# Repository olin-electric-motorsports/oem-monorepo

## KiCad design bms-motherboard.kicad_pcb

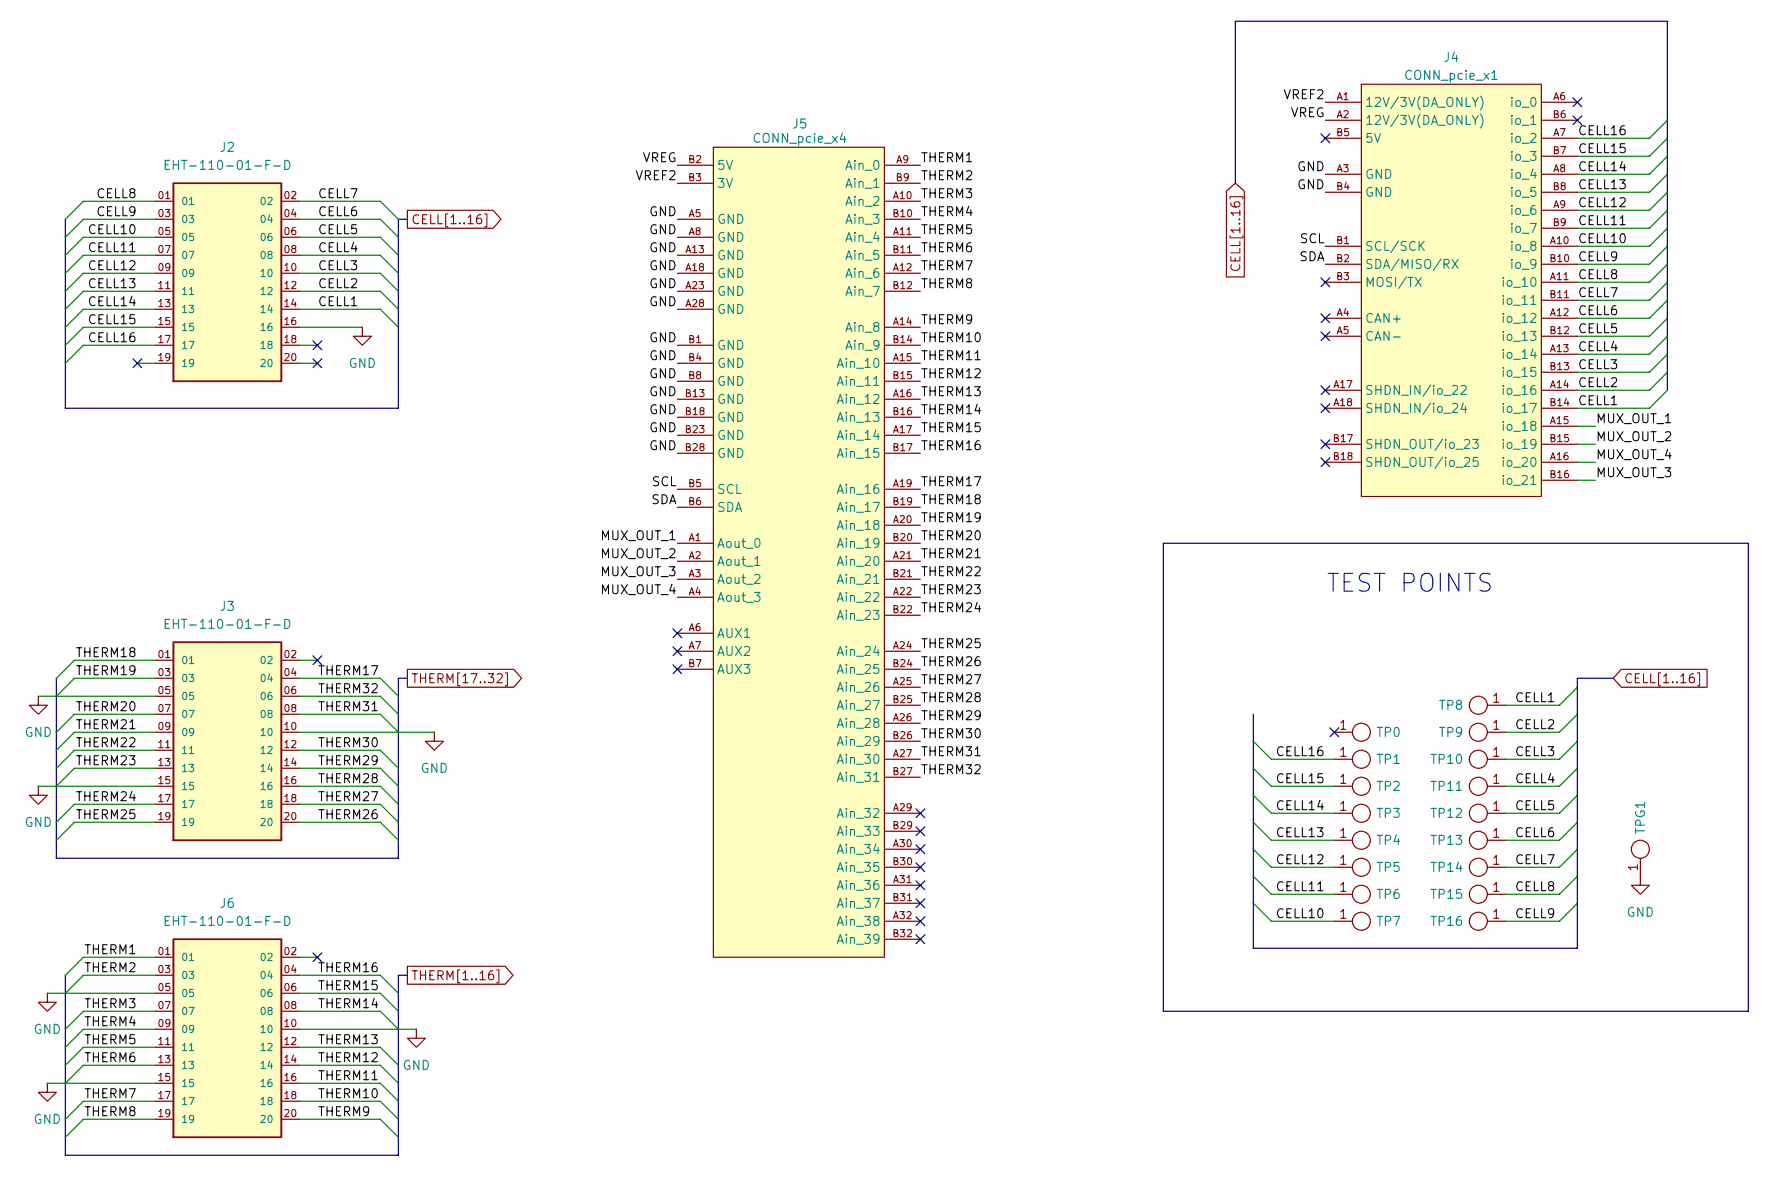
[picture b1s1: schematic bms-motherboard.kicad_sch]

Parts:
J2, J3, J6: EHT-110-01-F-D; SAMTEC_EHT-110-01-X-D (J_EHT-110-01-F-D); MPN EHT-110-01-F-D
J4: CONN_pcie_x1; te_pcie_x1_connector
J5: CONN_pcie_x4; te_pcie_x4_connector
TP0, TP1, TP2, TP3, TP4, TP5, TP6, TP7, TP8, TP9, TP10, TP11, TP12, TP13, TP14, TP15, TP16: TP_SMD; Test_Point_SMD; MPN 5019
TPG1: TP_SMD; Test_Point_SMD; MPN 5019

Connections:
/MUX_OUT_1: J4.A15 (io_18), J5.A1 (Aout_0)
/MUX_OUT_2: J4.B15 (io_19), J5.A2 (Aout_1)
/MUX_OUT_3: J4.B16 (io_21), J5.A3 (Aout_2)
/MUX_OUT_4: J4.A16 (io_20), J5.A4 (Aout_3)
/SCL: J4.B1 (SCL/SCK), J5.B5 (SCL)
/SDA: J4.B2 (SDA/MISO/RX), J5.B6 (SDA)
/VREF2: J4.A1 (12V/3V(DA_ONLY)), J5.B3 (3V)
/VREG: J4.A2 (12V/3V(DA_ONLY)), J5.B2 (5V)
CELL1: J2.14, J4.B14 (io_17), TP8.1
CELL2: J2.12, J4.A14 (io_16), TP9.1
CELL3: J2.10, J4.B13 (io_15), TP10.1
CELL4: J2.08, J4.A13 (io_14), TP11.1
CELL5: J2.06, J4.B12 (io_13), TP12.1
CELL6: J2.04, J4.A12 (io_12), TP13.1
CELL7: J2.02, J4.B11 (io_11), TP14.1
CELL8: J2.01, J4.A11 (io_10), TP15.1
CELL9: J2.03, J4.B10 (io_9), TP16.1
CELL10: J2.05, J4.A10 (io_8), TP7.1
CELL11: J2.07, J4.B9 (io_7), TP6.1
CELL12: J2.09, J4.A9 (io_6), TP5.1
CELL13: J2.11, J4.B8 (io_5), TP4.1
CELL14: J2.13, J4.A8 (io_4), TP3.1
CELL15: J2.15, J4.B7 (io_3), TP2.1
CELL16: J2.17, J4.A7 (io_2), TP1.1
GND: J2.16, J3.05, J3.10, J3.15, J4.A3 (GND), J4.B4 (GND), J5.A5 (GND), J5.A8 (GND), J5.A13 (GND), J5.A18 (GND), J5.A23 (GND), J5.A28 (GND), J5.B1 (GND), J5.B4 (GND), J5.B8 (GND), J5.B13 (GND), J5.B18 (GND), J5.B23 (GND), J5.B28 (GND), J6.05, J6.10, J6.15, TPG1.1; also elsewhere on the board
THERM1: J5.A9 (Ain_0), J6.01
THERM2: J5.B9 (Ain_1), J6.03
THERM3: J5.A10 (Ain_2), J6.07
THERM4: J5.B10 (Ain_3), J6.09
THERM5: J5.A11 (Ain_4), J6.11
THERM6: J5.B11 (Ain_5), J6.13
THERM7: J5.A12 (Ain_6), J6.17
THERM8: J5.B12 (Ain_7), J6.19
THERM9: J5.A14 (Ain_8), J6.20
THERM10: J5.B14 (Ain_9), J6.18
THERM11: J5.A15 (Ain_10), J6.16
THERM12: J5.B15 (Ain_11), J6.14
THERM13: J5.A16 (Ain_12), J6.12
THERM14: J5.B16 (Ain_13), J6.08
THERM15: J5.A17 (Ain_14), J6.06
THERM16: J5.B17 (Ain_15), J6.04
THERM17: J3.04, J5.A19 (Ain_16)
THERM18: J3.01, J5.B19 (Ain_17)
THERM19: J3.03, J5.A20 (Ain_18)
THERM20: J3.07, J5.B20 (Ain_19)
THERM21: J3.09, J5.A21 (Ain_20)
THERM22: J3.11, J5.B21 (Ain_21)
THERM23: J3.13, J5.A22 (Ain_22)
THERM24: J3.17, J5.B22 (Ain_23)
THERM25: J3.19, J5.A24 (Ain_24)
THERM26: J3.20, J5.B24 (Ain_25)
THERM27: J3.18, J5.A25 (Ain_26)
THERM28: J3.16, J5.B25 (Ain_27)
THERM29: J3.14, J5.A26 (Ain_28)
THERM30: J3.12, J5.B26 (Ain_29)
THERM31: J3.08, J5.A27 (Ain_30)
THERM32: J3.06, J5.B27 (Ain_31)

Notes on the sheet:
TEST POINTS

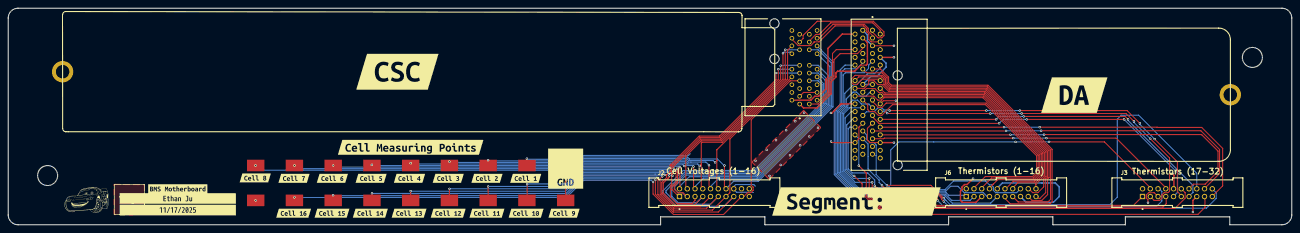
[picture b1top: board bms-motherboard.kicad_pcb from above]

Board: 2 copper layers, 331.3 x 55.9 mm, 49 parts (0 on the bottom side), 57 nets.

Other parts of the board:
H1, H2: CONN_MountingHole; PCIe_Mount
kibuzzard-691BC27F: G***; kibuzzard-691BC27F
kibuzzard-691BC245: G***; kibuzzard-691BC245
kibuzzard-691BC298: G***; kibuzzard-691BC298
kibuzzard-6747A1EF: G***; kibuzzard-6747A1EF
kibuzzard-6747A1F5: G***; kibuzzard-6747A1F5
kibuzzard-6747A1FA: G***; kibuzzard-6747A1FA
kibuzzard-6747A20D: G***; kibuzzard-6747A20D
kibuzzard-6747A21A: G***; kibuzzard-6747A21A
kibuzzard-6747A21D: G***; kibuzzard-6747A21D
kibuzzard-6747A22C: G***; kibuzzard-6747A22C
kibuzzard-6747A22F: G***; kibuzzard-6747A22F
kibuzzard-6747A069: G***; kibuzzard-6747A069
kibuzzard-6747A200: G***; kibuzzard-6747A200
kibuzzard-6747A204: G***; kibuzzard-6747A204
kibuzzard-6747A209: G***; kibuzzard-6747A209
kibuzzard-6747A211: G***; kibuzzard-6747A211
kibuzzard-6747A215: G***; kibuzzard-6747A215
kibuzzard-6747A222: G***; kibuzzard-6747A222
kibuzzard-6747A229: G***; kibuzzard-6747A229
kibuzzard-6747A319: G***; kibuzzard-6747A319
kibuzzard-6747A384: G***; kibuzzard-6747A384
kibuzzard-6747F2A5: G***; kibuzzard-6747F2A5
kibuzzard-67479E66: G***; kibuzzard-67479E66
kibuzzard-67479E86: G***; kibuzzard-67479E86

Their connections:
GND: H2.1; also elsewhere on the board

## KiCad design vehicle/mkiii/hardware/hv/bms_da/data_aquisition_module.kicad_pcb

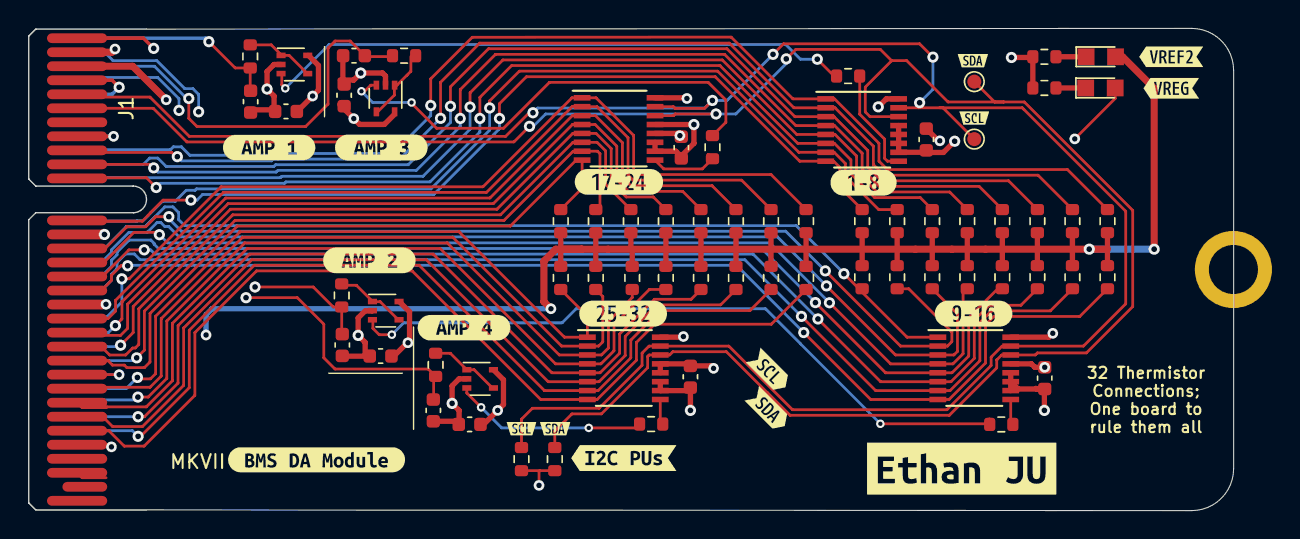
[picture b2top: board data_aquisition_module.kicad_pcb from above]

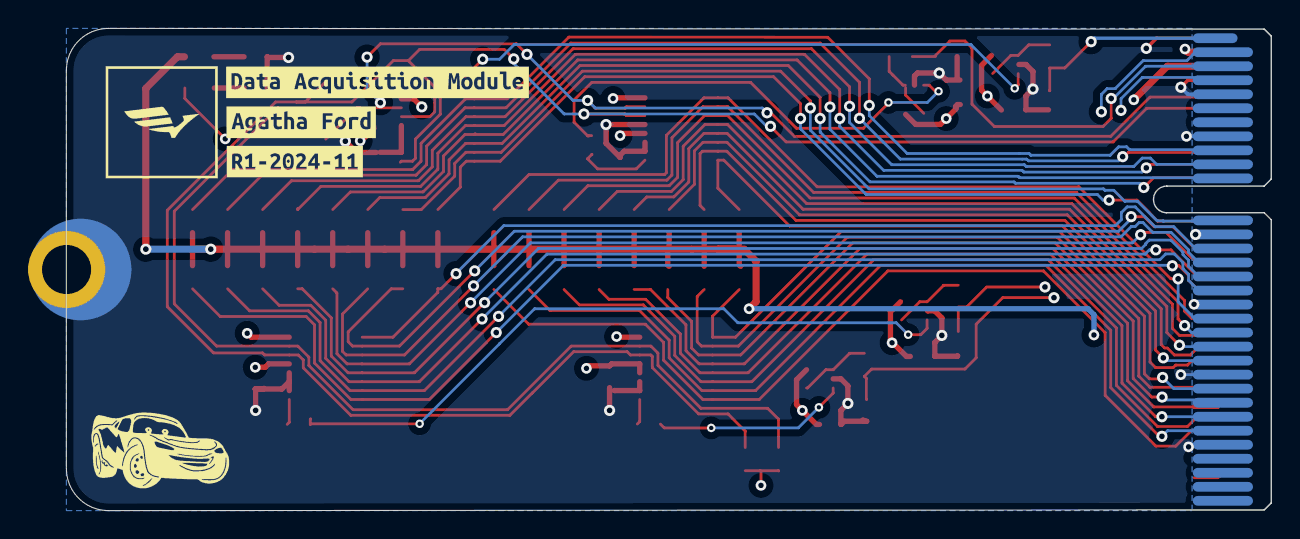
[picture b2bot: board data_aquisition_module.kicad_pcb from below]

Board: 4 copper layers, 86.0 x 34.4 mm, 92 parts (3 on the bottom side), 55 nets.

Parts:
C1, C2, C3, C4: C_1uF; C_0603
C5, C6, C7, C8, C9, C10, C11, C12: 1uF; C_0603
H2: CONN_MountingHole; PCIe_Mount
J1: CONN_pcie_x4; pcie_x4
PD1, PD2: WHITE; CHIPLED_0805
R1, R2, R3, R4, R5, R6, R7, R8, R9, R10, R11, R12, R13, R14, R15, R16, R17, R18, R19, R20, R21, R22, R23, R24, R25, R26, R27, R28, R29, R30, R31, R32: R_100K; R_0603
R33, R35, R37, R39: 1M; R_0603
R34, R36, R38, R40: 3.3K; R_0603
R41, R42: 1KR; R_0603
R43, R44: 4.7K; R_0603
TP1, TP2: TP_1mm; TestPoint_Pad_D1.0mm
U1, U2, U3, U4: LTC1380IGN; SSOP-16_3.9x4.9mm_P0.635mm
U5, U6, U7, U8: MCP6001T-I-LT; SOT-353_SC-70-5
kibuzzard-63A54BB0: G***; kibuzzard-63A54BB0
kibuzzard-63A54BCB: G***; kibuzzard-63A54BCB
kibuzzard-63A54BE3: G***; kibuzzard-63A54BE3
kibuzzard-63BF51CA: G***; kibuzzard-63BF51CA
kibuzzard-63BF55B8: G***; kibuzzard-63BF55B8
kibuzzard-63BF55D1: G***; kibuzzard-63BF55D1
kibuzzard-672C3C6B, kibuzzard-672C3C6B#2: G***; kibuzzard-672C3C6B
kibuzzard-672C3C52, kibuzzard-672C3C52#2: G***; kibuzzard-672C3C52
kibuzzard-672C38BF: G***; kibuzzard-672C38BF
kibuzzard-672D5DF4: G***; kibuzzard-672D5DF4
kibuzzard-673B8AB7: G***; kibuzzard-673B8AB7
kibuzzard-673B8ABD: G***; kibuzzard-673B8ABD
kibuzzard-673B8BCC: G***; kibuzzard-673B8BCC
kibuzzard-673B8DE4: G***; kibuzzard-673B8DE4
kibuzzard-673B8DEE: G***; kibuzzard-673B8DEE
kibuzzard-691BC3E8: G***; kibuzzard-691BC3E8
kibuzzard-66171EA1: G***; kibuzzard-66171EA1
kibuzzard-66171EC5: G***; kibuzzard-66171EC5
kibuzzard-661723CB: G***; kibuzzard-661723CB
kibuzzard-661723F5: G***; kibuzzard-661723F5

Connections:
/MUX_1_OUT: C12.1, J1.A1 (Aout_0), R34.1
/MUX_2_OUT: C10.1, J1.A2 (Aout_1), R36.1
/MUX_3_OUT: C8.1, J1.A3 (Aout_2), R38.1
/MUX_4_OUT: C6.1, J1.A4 (Aout_3), R40.1
/SCL: J1.B5 (SCL), R43.1, TP1.1, U1.15 (SCL), U2.15 (SCL), U3.15 (SCL), U4.15 (SCL)
/SDA: J1.B6 (SDA), R44.1, TP2.1, U1.14 (SDA), U2.14 (SDA), U3.14 (SDA), U4.14 (SDA)
/THERM_1: J1.A9 (Ain_0), R1.2, U1.1 (S0)
/THERM_2: J1.B9 (Ain_1), R2.2, U1.2 (S1)
/THERM_3: J1.A10 (Ain_2), R3.2, U1.3 (S2)
/THERM_4: J1.B10 (Ain_3), R4.2, U1.4 (S3)
/THERM_5: J1.A11 (Ain_4), R5.2, U1.5 (S4)
/THERM_6: J1.B11 (Ain_5), R6.2, U1.6 (S5)
/THERM_7: J1.A12 (Ain_6), R7.2, U1.7 (S6)
/THERM_8: J1.B12 (Ain_7), R8.2, U1.8 (S7)
/THERM_9: J1.A14 (Ain_8), R9.2, U2.1 (S0)
/THERM_10: J1.B14 (Ain_9), R10.2, U2.2 (S1)
/THERM_11: J1.A15 (Ain_10), R11.2, U2.3 (S2)
/THERM_12: J1.B15 (Ain_11), R12.2, U2.4 (S3)
/THERM_13: J1.A16 (Ain_12), R13.2, U2.5 (S4)
/THERM_14: J1.B16 (Ain_13), R14.2, U2.6 (S5)
/THERM_15: J1.A17 (Ain_14), R15.2, U2.7 (S6)
/THERM_16: J1.B17 (Ain_15), R16.2, U2.8 (S7)
/THERM_17: J1.A19 (Ain_16), R17.2, U3.1 (S0)
/THERM_18: J1.B19 (Ain_17), R18.2, U3.2 (S1)
/THERM_19: J1.A20 (Ain_18), R19.2, U3.3 (S2)
/THERM_20: J1.B20 (Ain_19), R20.2, U3.4 (S3)
/THERM_21: J1.A21 (Ain_20), R21.2, U3.5 (S4)
/THERM_22: J1.B21 (Ain_21), R22.2, U3.6 (S5)
/THERM_23: J1.A22 (Ain_22), R23.2, U3.7 (S6)
/THERM_24: J1.B22 (Ain_23), R24.2, U3.8 (S7)
/THERM_25: J1.A24 (Ain_24), R25.2, U4.1 (S0)
/THERM_26: J1.B24 (Ain_25), R26.2, U4.2 (S1)
/THERM_27: J1.A25 (Ain_26), R27.2, U4.3 (S2)
/THERM_28: J1.B25 (Ain_27), R28.2, U4.4 (S3)
/THERM_29: J1.A26 (Ain_28), R29.2, U4.5 (S4)
/THERM_30: J1.B26 (Ain_29), R30.2, U4.6 (S5)
/THERM_31: J1.A27 (Ain_30), R31.2, U4.7 (S6)
/THERM_32: J1.B27 (Ain_31), R32.2, U4.8 (S7)
/VREF2: J1.B3 (3V), PD2.2 (A), R1.1, R2.1, R3.1, R4.1, R5.1, R6.1, R7.1, R8.1, R9.1, R10.1, R11.1, R12.1, R13.1, R14.1, R15.1, R16.1, R17.1, R18.1, R19.1, R20.1, R21.1, R22.1, R23.1, R24.1, R25.1, R26.1, R27.1, R28.1, R29.1, R30.1, R31.1, R32.1
/VREG: C1.1, C2.1, C3.1, C4.1, C5.1, C7.1, C9.1, C11.1, J1.B2 (5V), PD1.2 (A), R43.2, R44.2, U1.16 (VCC), U2.13 (A0), U2.16 (VCC), U3.12 (A1), U3.16 (VCC), U4.12 (A1), U4.13 (A0), U4.16 (VCC), U5.5 (V+), U6.5 (V+), U7.5 (V+), U8.5 (V+)
GND: C1.2, C2.2, C3.2, C4.2, C5.2, C6.2, C7.2, C8.2, C9.2, C10.2, C11.2, C12.2, H2.1, J1.A5 (GND), J1.A8 (GND), J1.A13 (GND), J1.A18 (GND), J1.A23 (GND), J1.A28 (GND), J1.B1 (GND), J1.B4 (GND), J1.B8 (GND), J1.B13 (GND), J1.B18 (GND), J1.B23 (GND), J1.B28 (GND), R41.2, R42.2, U1.10 (VEE), U1.11 (GND), U1.12 (A1), U1.13 (A0), U2.10 (VEE), U2.11 (GND), U2.12 (A1), U3.10 (VEE), U3.11 (GND), U3.13 (A0), U4.10 (VEE), U4.11 (GND), U5.2 (V-), U6.2 (V-), U7.2 (V-), U8.2 (V-)
unnamed: PD1.1 (K), R41.1
unnamed: PD2.1 (K), R42.1
unnamed: R33.1, U1.9 (D0)
unnamed: R35.1, U2.9 (D0)
unnamed: R37.1, U3.9 (D0)
unnamed: R39.1, U4.9 (D0)
unnamed: R39.2, U5.3 (+)
unnamed: R40.2, U5.1, U5.4 (-)
unnamed: R37.2, U6.3 (+)
unnamed: R38.2, U6.1, U6.4 (-)
unnamed: R35.2, U7.3 (+)
unnamed: R36.2, U7.1, U7.4 (-)
unnamed: R33.2, U8.3 (+)
unnamed: R34.2, U8.1, U8.4 (-)

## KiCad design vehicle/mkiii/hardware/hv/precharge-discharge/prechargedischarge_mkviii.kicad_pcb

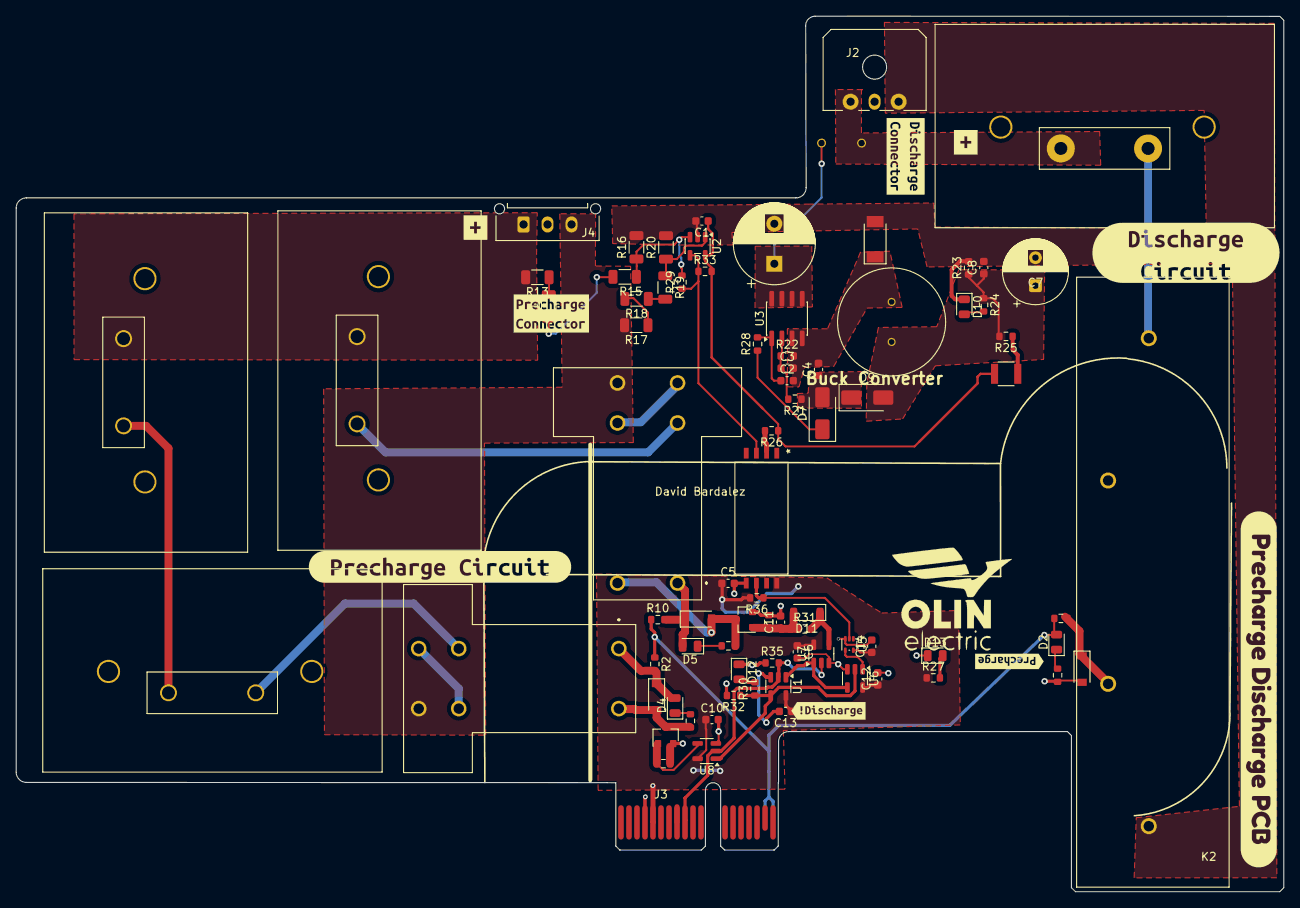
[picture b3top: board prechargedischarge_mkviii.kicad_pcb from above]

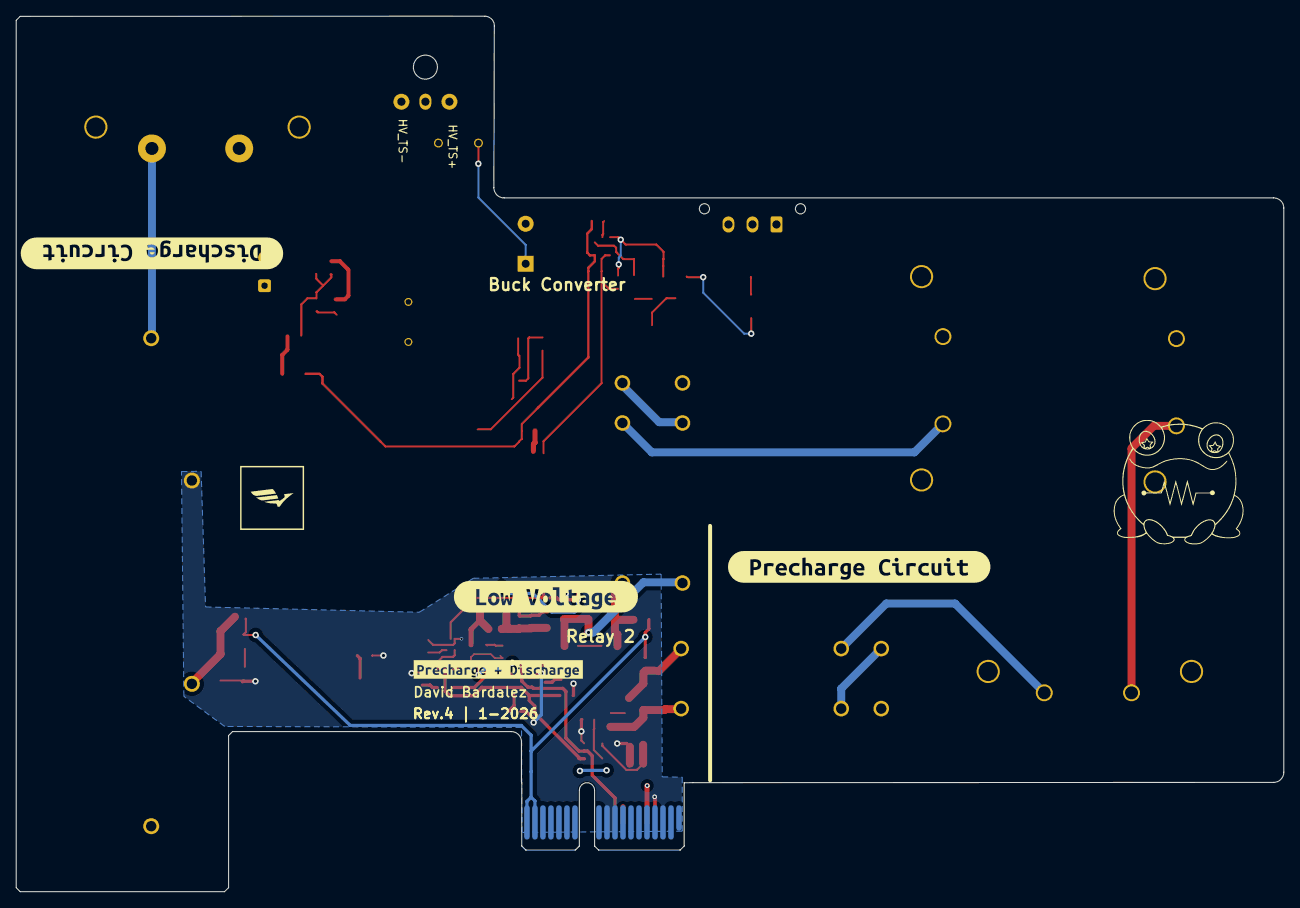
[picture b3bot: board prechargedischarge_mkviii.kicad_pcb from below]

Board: 2 copper layers, 158.4 x 109.4 mm, 94 parts (4 on the bottom side), 49 nets.

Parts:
C1, C5, C6, C10, C14: 0.1 µF; C_0603_1608Metric
C2: C_2.2uF; C_0603_1608Metric
C3: C_470pF; C_0603_1608Metric
C4: C_.22uF; C_0603_1608Metric
C7: 100uF+; CP_Radial_D8.0mm_P3.50mm
C8: C_1uF; C_0603_1608Metric
C9: 10uF+; CP_Radial_D10.0mm_P5.00mm
C11: C_2.2uF_25V; C_0603_1608Metric
C12, C13: C_0.1uF; C_0603_1608Metric
D1, D3, D6: SS110LW; D_SOD-123
D2, D4, D5: LED_WHITE; D_0805_2012Metric
D7, D9: STTH1R06AF; D_SMA
D8: STTH1R06AF; D_SOD-128
D10, D13: LED_WHITE; LED_0805_2012Metric
D11: 1N4148W; D_SOD-123
D12: BSPD_TRIP_LED; D_0805_2012Metric
F1: F_21mA_420V
F2: F_500mA_16V; Fuse_1210
J2: Conn_01x03_Pin; Molex_Micro-Fit_3.0_43650-0300_1x03_P3.00mm_Horizontal
J3: CONN_pcie_x1; pcie_x1
J4: Conn_01x03_Pin; Molex_Micro-Fit_3.0_43650-0315_1x03_P3.00mm_Vertical
K1, K3: G2RG-2A-X_DC12; K_Relay_DPST_NO_10A_12V_TH
K2: 3350-4275-126; Relay_Comus_3350
L1: L_1.2mH
Q1, Q2: SSM3K333R; SOT-23F
R1: 10KR; R_0603
R2, R10: 12R; R_0603_1608Metric
R3, R4: 560R-100W; R_TO247-Heatsink
R5: 12R; R_0603
R6: 3KR-100W; R_TO247-Heatsink
R7, R8, R11: 1KR; R_0603
R9: 120R-100W; R_TO247-Heatsink
R12: 270kR; R_0603
R13, R14, R17, R18: 2.2 MΩ; R_1206_3216Metric
R15, R19: 330 kΩ; R_1206_3216Metric
R16: 36 kΩ; R_1206_3216Metric
R20: 25 kΩ; R_1206_3216Metric
R21: R_71.5K; R_0603_1608Metric
R22: R_6.04K; R_0603_1608Metric
R23: R_3K; R_0603_1608Metric
R24, R27, R30: R_1K; R_0603_1608Metric
R25: R_0_2512; R_0603_1608Metric
R26: 330Ω; R_0603_1608Metric
R28, R32: R_10K; R_0603_1608Metric
R29: R_4.7M; R_0603_1608Metric
R31: R_71.5k; R_0603_1608Metric
R33, R36: R_10k; R_0603_1608Metric
R35: 100 kΩ; R_0603_1608Metric
U1, U6: U_GATE_SN74LVC1G02DBVR; SOT-23-5
U2: LM397; SOT-23-5
U3: MP9488; SOIC-8_3.9x4.9mm_P1.27mm
U4: ACNT-H50L-500E
U5: 74LVC1GU04DRL; SOT-553
U7, U8: SN74LVC1G08DBVR; SOT-23-5
kibuzzard-679E7E49, kibuzzard-679E7E49#2: G***; kibuzzard-679E7E49
kibuzzard-679E7E71: G***; kibuzzard-679E7E71
kibuzzard-679E7EA1: G***; kibuzzard-679E7EA1
kibuzzard-679E816B: G***; kibuzzard-679E816B
kibuzzard-679E8163: G***; kibuzzard-679E8163
kibuzzard-679E8270: G***; kibuzzard-679E8270
kibuzzard-679EBF0B, kibuzzard-679EBF0B#2: G***; kibuzzard-679EBF0B
kibuzzard-6784D6A3: G***; kibuzzard-6784D6A3
kibuzzard-6784D6E2: G***; kibuzzard-6784D6E2
kibuzzard-6784D698: G***; kibuzzard-6784D698
kibuzzard-639639B8: G***; kibuzzard-639639B8

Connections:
+5V: C5.1, C6.1, C10.1, C12.1, C13.1, C14.1, J3.B5 (5V), R27.1, R36.2, U1.5 (VCC), U4.8, U5.5 (VCC), U6.5 (VCC), U7.5 (VCC), U8.5 (VCC)
/+5V_TS_FUSED: C1.1, F2.1, R26.1, R33.2, U2.5 (V+)
/DONE_ISO: R36.1, U4.6, U5.2
/DONE_ISO_N: U5.4, U6.1 (in)
/DONE_LATCHED: U1.1 (in), U6.4 (out), U7.1
/DONE_LATCHED_N: R30.1, R32.1, U1.4 (out), U6.2 (in), U8.1
/FB: C3.1, R21.2, R22.1, U3.2 (FB)
/FINAL_SHUTDOWN: D2.2 (A), J3.A17 (SHDN_IN/io_22), J3.A18 (SHDN_IN/io_24), R2.1, R5.1, R10.1
/HV_BAT+: J4.1, R4.1, R9.1, R13.2
/HV_TS+: F1.2, J2.1, R6.1
/HV_TS+_Fuse: J4.3, K1.5 (NO_(-)), K3.5 (NO_(-)), R17.2
/HV_TS-: C1.2, C7.2, C8.2, C9.2, D8.2 (A), D10.1 (K), J2.3, K2.1, R16.2, R20.2, R23.2, U2.2 (V-)
/PRECHARGE_DONE_N: R29.1, R33.1, U2.4, U4.3
/PRECHARGE_LSD: J3.B9 (io_7), R35.2, U1.2 (in), U7.2, U8.2
/PRECHARGE_LSD_1: Q1.1 (G), R1.1, U8.4
/PRECHARGE_LSD_2: D11.1 (K), R31.2, U7.4
/SW: C2.2, C3.2, C4.2, D8.1 (K), L1.1, R22.2, U3.3 (SW), U3.4 (SW)
/TS+_FUSED: C9.1, F1.1, U3.5 (NC), U3.6 (NC), U3.7 (VIN), U3.8 (NC)
/VCC: C2.1, R28.2, U3.1 (VCC)
/V_DC_SENSE: R15.1, R16.1, R29.2, U2.3 (+)
/V_PACK_SENSE: R19.1, R20.1, U2.1 (-)
GND: C5.2, C6.2, C10.2, C11.2, C12.2, C13.2, C14.2, D3.2 (A), D12.1 (K), D13.1 (K), J3.A3 (GND), J3.A9 (io_6), J3.A10 (io_8), J3.B4 (GND), K2.3 (-), Q1.2 (S), Q2.2 (S), R1.2, R7.2, R12.2, R32.2, R35.1, U1.3 (GND), U4.5, U5.3 (GND), U6.3 (GND), U7.3 (GND), U8.3 (GND)
unnamed: D1.2 (A), K1.8 (COIL_2), Q1.3 (D), R8.2
unnamed: D1.1 (K), D4.2 (A), K1.1 (COIL_1), R2.2
unnamed: D2.1 (K), R7.1
unnamed: D3.1 (K), K2.2 (+), R5.2
unnamed: D4.1 (K), R8.1
unnamed: D5.2 (A), D6.1 (K), K3.1 (COIL_1), R10.2
unnamed: D5.1 (K), R11.1
unnamed: D6.2 (A), K3.8 (COIL_2), Q2.3 (D), R11.2
unnamed: C4.1, D7.2 (A), D9.1 (K), R21.1
unnamed: D7.1 (K), R28.1
unnamed: C7.1, C8.1, D9.2 (A), L1.2, R23.1, R24.1, R25.2
unnamed: D10.2 (A), R24.2
unnamed: C11.1, D11.2 (A), Q2.1 (G), R12.1, R31.1
unnamed: D12.2 (A), R30.2
unnamed: D13.2 (A), R27.2
unnamed: F2.2, R25.1
unnamed: K1.4 (NO), K1.6 (COM)
unnamed: K1.3 (COM_(+)), R3.2
unnamed: K2.4, R6.2
unnamed: K3.4 (NO), K3.6 (COM)
unnamed: K3.3 (COM_(+)), R9.2
unnamed: R3.1, R4.2
unnamed: R13.1, R14.2
unnamed: R14.1, R15.2
unnamed: R17.1, R18.2
unnamed: R18.1, R19.2
unnamed: R26.2, U4.2

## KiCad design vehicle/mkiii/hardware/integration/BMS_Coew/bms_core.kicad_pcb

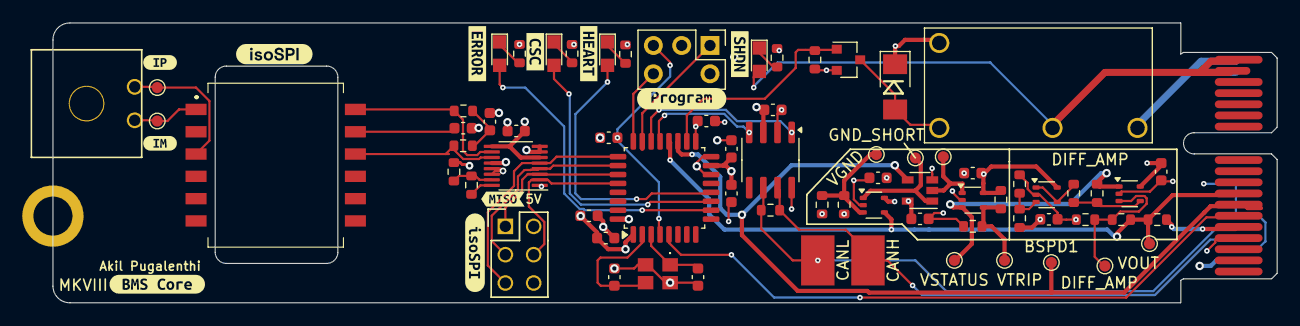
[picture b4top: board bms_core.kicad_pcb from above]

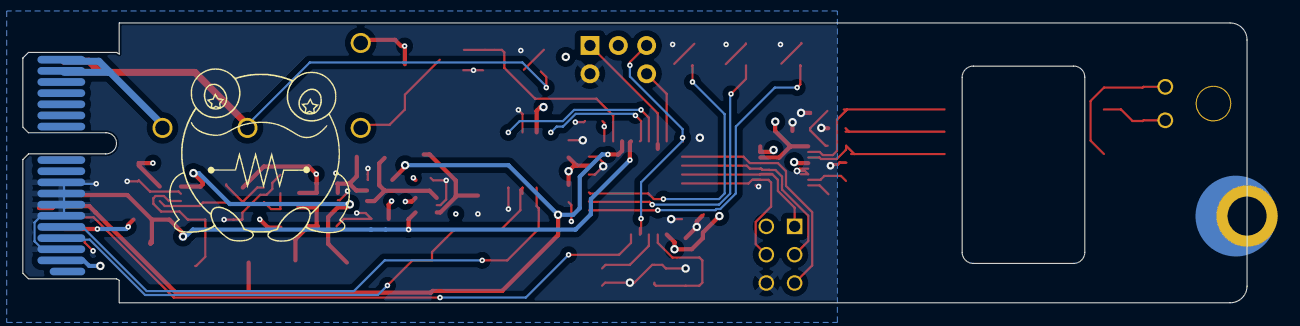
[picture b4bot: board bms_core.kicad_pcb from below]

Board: 4 copper layers, 109.8 x 25.1 mm, 86 parts (3 on the bottom side), 47 nets.

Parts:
BSPD1: BSPD_CURRENT_THRESH; TestPoint_Pad_D1.0mm
C6, C9, C10, C11, C12, C13: C_0.1uF; C_0603
C7, C8: C_10nF; C_0603
C14, C15: C_30pF_50V; C_0603_1608Metric
C16, C17, C18, C19, C20, C21, C22: C_0.1uF_16V; C_0603_1608Metric
CANH: CANH1; TP_Hook_SMD
CANL: CANL1; TP_Hook_SMD
CURRENT_TRIP: CURRENT_TRIP; TestPoint_Pad_D1.0mm
D1: LED_AMBER; CHIPLED_0805
D2: LED_GREEN; CHIPLED_0805
D3: LED_RED; CHIPLED_0805
D5: D_Zener_18V_SMBJ5355B-TP; DO-214AA
D6: LED_BLUE; CHIPLED_0805
DIFF_AMP: TP_1mm; TestPoint_Pad_D1.0mm
GND_SHORT: GND_SHORT; TestPoint_Pad_D1.0mm
H2: CONN_MountingHole; PCIe_Mount
IM1: TP_1mm; TestPoint_Pad_D1.0mm
IP1: TP_1mm; TestPoint_Pad_D1.0mm
J2: CONN_02x03; Pin_Header_Straight_2x03
J3: MicroFit_RA_2
J4: J_Programming_Pin_Header; J_Programming_Pin_Header_Keyed
J5: J_PCIe_x1; J_PCIe_x1_Key
K1: Relay_G5Q-1A4-DC5; Relay_SPST_OMRON-G5Q-1A4_OEM
Q1: SSM3K333R; SOT-23F
R1, R3, R21, R23: 1KR; R_0603
R5: R_120_DNP; R_0603
R7, R12, R13, R14, R15, R16, R19, R24, R25: R_10K; R_0603
R8, R9, R18: R_1K; R_0603
R10, R11: R_60.4; R_0603
R17: R_1M; R_0603
R20: R_576; R_0603
T1: HM2112ZNLT
U3: LTC6820HMS; MSOP-16_3x4mm_P0.5mm
U4, U5, U6, U8: MCP6001; SOT-353_SC-70-5
U7: SN74LVC1G32DBVR; SOT-23-5_OEM
U10: STM32G441KBT6; LQFP-32_7x7mm_P0.8mm
U11: MCP2561-E_SN; SOIC-8_3.9x4.9mm_P1.27mm
VGND: V_GND_THRESHOLD; TestPoint_Pad_D1.0mm
VOUT: VOUT; TestPoint_Pad_D1.0mm
VSTATUS: VSTATUS; TestPoint_Pad_D1.0mm
VTRIP: VTRIP; TestPoint_Pad_D1.0mm
Y3: X_16MHz_18pF; FA238160000MBC0 (X_16MHz_18pF_SMD - FA-238_16.0000MB-C0)
kibuzzard-63B930AD: G***; kibuzzard-63B930AD
kibuzzard-63B9305B: G***; kibuzzard-63B9305B
kibuzzard-63B93076: G***; kibuzzard-63B93076
kibuzzard-63BB8A3F: G***; kibuzzard-63BB8A3F
kibuzzard-63BB8A53: G***; kibuzzard-63BB8A53
kibuzzard-63BF4A21: G***; kibuzzard-63BF4A21
kibuzzard-63BF57C4: G***; kibuzzard-63BF57C4
kibuzzard-673AE5D1: G***; kibuzzard-673AE5D1
kibuzzard-673AE69E: G***; kibuzzard-673AE69E
kibuzzard-673AE93C: G***; kibuzzard-673AE93C
kibuzzard-673AE677: G***; kibuzzard-673AE677
kibuzzard-673AE688: G***; kibuzzard-673AE688
kibuzzard-673AE955: G***; kibuzzard-673AE955
kibuzzard-673AE966: G***; kibuzzard-673AE966

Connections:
+3V3: C16.1, C17.1, C18.1, C19.1, C20.1, J4.3, J5.A2 (3.3V), U10.1 (VDD), U10.15 (VDDA), U10.17 (VDD)
+5V: C6.1, C9.1, C10.1, C11.1, C12.1, C13.1, C22.1, D5.1 (K), J2.2, J5.B5 (5V), K1.5, R12.2, R17.1, R19.2, R24.1, U3.6 (VDDS), U3.7 (POL), U3.8 (PHA), U3.9 (VDD), U3.12 (MSTR), U4.5 (V+), U5.5 (V+), U6.5 (V+), U7.5 (VCC), U8.5 (V+), U11.3 (VDD)
/BMS_RELAY_DRIVE: Q1.1 (G), R7.2, U10.18 ((TIM4_ETR/USART1_CK/GPIO_EXTI8)PA8)
/BSPD Current Sensor Trigger/CURRENT_TRIP: CURRENT_TRIP.1, U6.1, U7.2 (in)
/BSPD Current Sensor Trigger/GND_SHORT: GND_SHORT.1, U5.1, U7.1 (in)
/BSPD Current Sensor Trigger/VSTATUS: R15.2, U4.1, U6.3 (+), VSTATUS.1
/BSPD Current Sensor Trigger/VTRIP: R19.1, R20.1, U6.4 (-), VTRIP.1
/BSPD Current Sensor Trigger/V_GND_THRESHOLD: R17.2, R18.1, U5.3 (+), VGND.1
/BSPD_CURRENT_THRESH: BSPD1.1, J5.B7 (io_3), U7.4 (out), U10.19 ((TIM2_CH3/TIM15_BKIN/USART1_TX/GPIO_EXT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)
/CANH: CANH.1, J5.A4 (CAN+), R5.1, U11.7 (CANH)
/CANL: CANL.1, J5.A5 (CAN-), R5.2, U11.6 (CANL)
/CAN_RX: U10.21 ((FDCAN1_RX/GPIO_EXTI11)PA11), U11.4 (RXD)
/CAN_TX: U10.22 ((FDCAN1_TX/GPIO_EXTI12)PA12), U11.1 (TXD)
/CSC_Comms: D2.2 (A), U10.11 ((TIM3_CH1/TIM16_CH1/GPIO_EXTI6/ADC2_IN3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)
/Error: D3.2 (A), U10.10 ((TIM2_ETR/TIM2_CH1/GPIO_EXTI5/ADC2_IN13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)
/FAN_PWM: J5.B6 (io_1), U10.5 ((TIM2_ETR/TIM2_CH1/GPIO_EXTI0/ADC2_IN1/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)
/Heartbeat: D1.2 (A), U10.12 ((TIM3_CH2/TIM17_CH1/GPIO_EXTI7/ADC2_IN4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)
/IM: IM1.1, J3.1, T1.1
/IP: IP1.1, J3.2, T1.3
/ISO_CS: J2.5, U3.5 (~CS), U10.25 ((TIM2_ETR/TIM2_CH1/GPIO_EXTI15)PA15)
/ISO_MISO: J2.1, U3.3 (MISO), U10.27 ((TIM17_BKIN/SPI1_MISO/TIM3_CH1/TIM16_CH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)
/ISO_MOSI: J2.4, U3.2 (MOSI), U10.28 ((TIM17_CH1/SPI1_MOSI/TIM3_CH2/TIM16_BKI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)
/ISO_SCK: J2.3, U3.4 (SCK), U10.26 ((TIM3_ETR/SPI1_SCK/TIM4_ETR/TIM2_CH2/GP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)
/NRST: C21.1, J4.4, U10.4 ((GPIO_EXTI10)PG10-NRST)
/SHDN_IN: J5.A17 (SHDN_IN/io_22), J5.A18 (SHDN_IN/io_24), K1.3
/SHDN_OUT: D6.2 (A), J5.B17 (SHDN_OUT/io_23), J5.B18 (SHDN_OUT/io_25), K1.2
/SWCLK: J4.5, U10.24 ((SYS_JTCK-SWCLK/GPIO_EXTI14)PA14)
/SWDIO: J4.1, U10.23 ((SYS_JTMS-SWDIO/GPIO_EXTI13)PA13)
/VOUT_CURRENT_SENSE: J5.B8 (io_5), R12.1, R13.1, U5.4 (-), U10.20 ((TIM2_CH4/USART1_RX/TIM17_BKIN/GPIO_EXT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), VOUT.1
GND: C6.2, C7.2, C8.2, C9.2, C10.2, C11.2, C12.2, C13.2, C14.2, C15.2, C16.2, C17.2, C18.2, C19.2, C20.2, C21.2, C22.2, J2.6, J4.2, J5.A3 (GND), J5.A6 (io_0), J5.A7 (io_2), J5.A8 (io_4), J5.A9 (io_6), J5.B4 (GND), Q1.2 (S), R1.2, R3.2, R7.1, R9.2, R14.1, R18.2, R20.2, R21.2, R23.2, R25.2, U3.1 (EN), U3.13 (SLOW), U3.14 (GND), U4.2 (V-), U5.2 (V-), U6.2 (V-), U7.3 (GND), U8.2 (V-), U10.14 (VSSA), U10.16 (VSS), U10.32 (VSS), U11.2 (VSS), U11.8 (STBY), Y3.2, Y3.4
unnamed: C7.1, R10.2, R11.1
unnamed: C8.1, T1.11
unnamed: D1.1 (K), R1.1
unnamed: D2.1 (K), R3.1
unnamed: D3.1 (K), R21.1
unnamed: D5.2 (A), K1.1, Q1.3 (D)
unnamed: D6.1 (K), R23.1
unnamed: R8.1, U3.16 (IBIAS)
unnamed: R8.2, R9.1, U3.15 (ICMP)
unnamed: R10.1, T1.12, U3.10 (IM)
unnamed: R11.2, T1.10, U3.11 (IP)
unnamed: DIFF_AMP.1, R13.2, R14.2, U4.3 (+)
unnamed: R15.1, R16.2, U4.4 (-)
unnamed: R24.2, R25.1, U8.3 (+)
unnamed: R16.1, U8.1, U8.4 (-)
unnamed: C15.1, U10.2 (PF0-OSC_IN), Y3.3
unnamed: C14.1, U10.3 (PF1-OSC_OUT), Y3.1

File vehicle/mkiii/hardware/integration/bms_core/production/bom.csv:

Designator,Footprint,Quantity,Value,LCSC Part #
"C1, C16, C17, C21, C22",0603,5,C_0.1uF_16V,C0603C104Z4VACTU
"C10, C11, C12, C13, C6, C9",C_0603,6,C_0.1uF,478-3352-1-ND
"C14, C15",0603,2,C_30pF_50V,CML0603C0G300JT50V
C18,0603,1,C_4.7uF_25V,GRT188R61E475ME13D
C19,0603,1,C_10nF_50V,CL10B103KB8NNNC
C20,0603,1,C_1uF_25V,CL10B105KA8NNNC
"C7, C8",C_0603,2,C_10nF,1276-1015-1-ND
CANH,TP_Hook_SMD,1,CANH1,5019
CANL,TP_Hook_SMD,1,CANL1,5019
D1,CHIPLED_0805,1,LED_AMBER,
D2,CHIPLED_0805,1,LED_GREEN,
D3,CHIPLED_0805,1,LED_RED,
D5,DO-214AA,1,D_Zener_18V_SMBJ5355B-TP,SMBJ5355B-TP
D6,CHIPLED_0805,1,LED_BLUE,LTST-C171TBKT
J1,PinHeader_2x03_P2.54mm_Vertical,1,isoSPI Header,
J3,MicroFit_RA_2,1,MicroFit_RA_2,WM1865-ND
J4,J_Programming_Pin_Header_Keyed,1,J_Programming_Pin_Header,
J5,J_PCIe_x1_Key,1,J_PCIe_x1,2-1761465-1
K1,Relay_SPST_OMRON-G5Q-1A4_OEM,1,Relay_G5Q-1A4-DC5,G5Q-1A4 DC5
Q1,SOT-23F,1,SSM3K333R,SSM3K333RLFCT-ND
"R1, R21, R23, R3",R_0603,4,1KR,RMCF0603FT1K00
"R10, R11",R_0603,2,R_60.4,P60.4DACT-ND
"R12, R15, R16, R19, R7",R_0603,5,R_10K,CRS0805-FX-1002ELFCT-ND
R17,R_0603,1,R_1M,RMCF0805JT1M00CT-ND
"R18, R8, R9",R_0603,3,R_1K,RNCP0805FTD1K00CT-ND
R2,0603,1,R_5.1k,CR0603AFX-5101EAS
R20,R_0603,1,R_576,RMCF0603FT576R
R24,R_0603,1,R_10K,RMCF0805JT1M00CT-ND
R25,R_0603,1,R_10K,RNCP0805FTD1K00CT-ND
R4,0603,1,R_10k,RMCF0603FT10K0
R5,0603,1,R_120,RC0603FR-13120RL
T1,HM2112ZNLT,1,HM2112ZNLT,HM2112ZNLT
"U1, U4, U5, U6, U8",SOT-353_SC-70-5,5,MCP6001,MCP6001T-I/OT
U10,LQFP-32_7x7mm_P0.8mm,1,STM32G441KBT6,
U11,SOIC-8_3.9x4.9mm_P1.27mm,1,MCP2561-E_SN,MCP2561-E/SN
U3,MSOP-16_3x4mm_P0.5mm,1,LTC6820HMS,LTC6820HMS#TRPBFCT-ND
U7,SOT-23-5_OEM,1,SN74LVC1G32DBVR,296-9847-1-ND
Y3,FA238160000MBC0 (X_16MHz_18pF_SMD - FA-238_16.0000MB-C0),1,X_16MHz_18pF,FA-238 16.0000MB-C0
